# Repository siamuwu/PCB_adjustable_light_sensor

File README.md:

# Adjustable Light Sensor (LDR + 555 Timer)

## Overview

This project is an **adjustable light-sensitive switching circuit** using an LDR, a potentiometer and a 555 Timer IC. The system detects ambient light intensity and automatically turns an LED ON or OFF based on a user-defined threshold. The sensitivity of the circuit can be tuned using the potentiometer which makes it adaptable for different lighting conditions.

## Features

* Automatic light detection using LDR
* Adjustable sensitivity via potentiometer
* Stable switching using 555 Timer IC
* Simple, low-cost analog design
* Suitable for real-world automation applications

## Components Used
* LDR (Light Dependent Resistor)
* Potentiometer
* 555 Timer IC
* LED
* Resistors
* Capacitor
* Power Supply (5V–9V)

## Working Principle

The LDR and potentiometer form a voltage divider that generates a voltage corresponding to ambient light intensity. This voltage is fed into the 555 Timer IC, which operates as a comparator.

* In **bright conditions**, the LDR resistance decreases, causing the output to remain OFF.
* In **low-light conditions**, the LDR resistance increases, and once the voltage crosses the threshold set by the potentiometer, the 555 Timer switches the LED ON.

The potentiometer allows fine-tuning of the switching point, enabling precise control over when the LED activates.

## Applications

* Automatic street lighting
* Night lamps
* Light-activated switches
* Energy-efficient lighting systems
* Basic sensor interfacing projects

## What I have learnt from this project
* Basic PCB Design by KiCad
* Usage of LDR for sensing light
* Usage of 555 Timer in various applications

## Preview

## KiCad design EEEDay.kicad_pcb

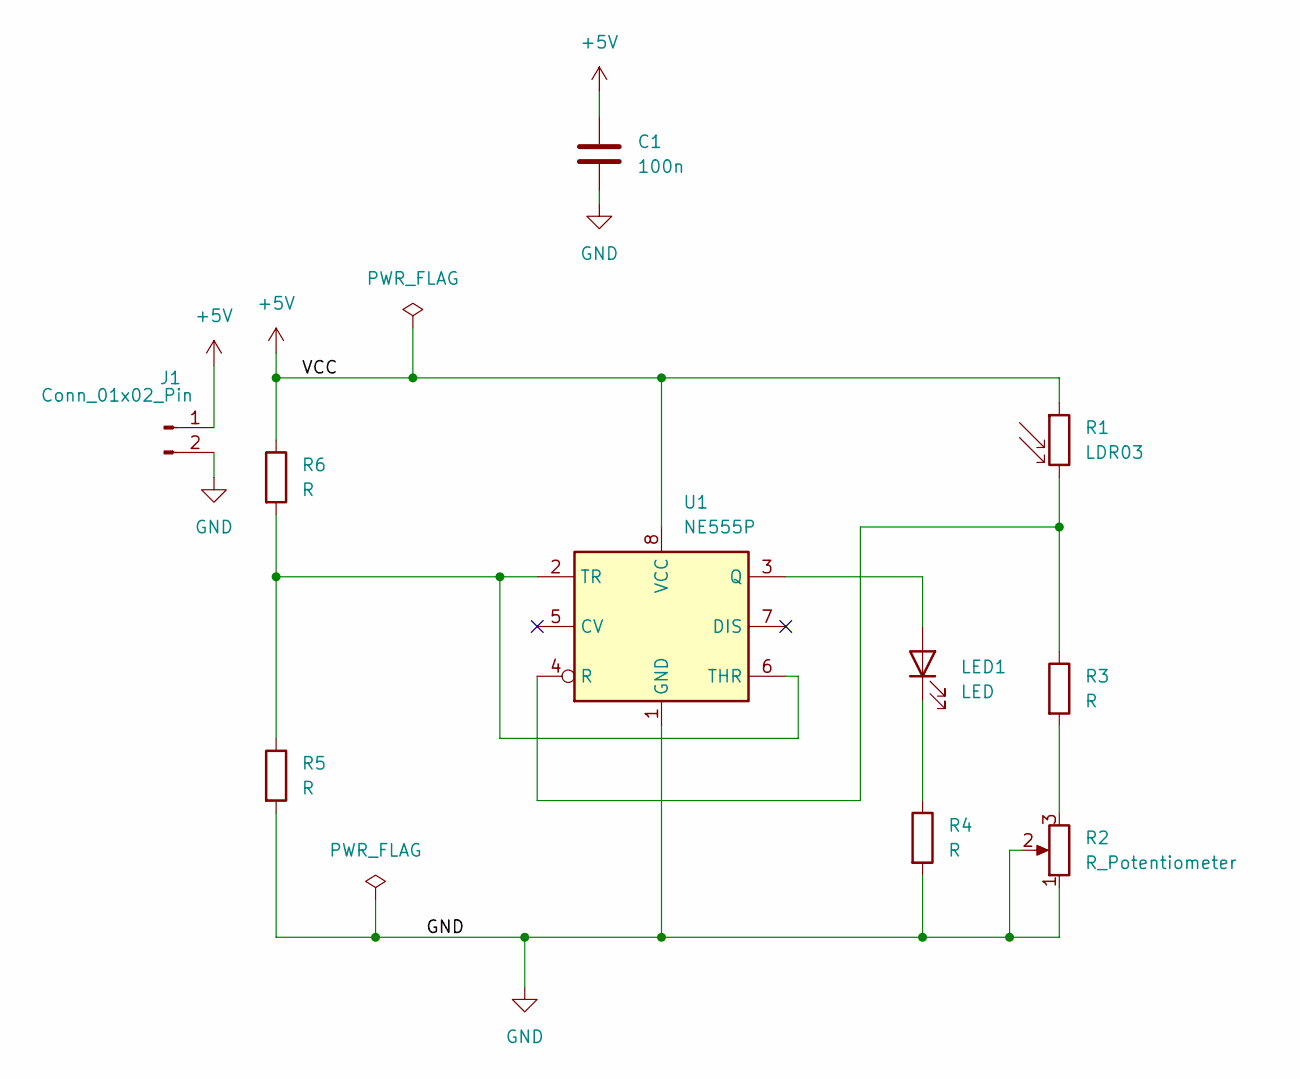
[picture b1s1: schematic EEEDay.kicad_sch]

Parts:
C1: 100n; C_Disc_D7.5mm_W5.0mm_P7.50mm
J1: Conn_01x02_Pin; AMASS_XT30PW-F_1x02_P2.50mm_Horizontal
LED1: LED; LED_D5.0mm
R1: LDR03; R_LDR_10x8.5mm_P7.6mm_Vertical
R2: R_Potentiometer; Potentiometer_Bourns_3296W_Vertical
R3, R4, R5, R6: R; R_Axial_DIN0207_L6.3mm_D2.5mm_P7.62mm_Horizontal
U1: NE555P; DIP-8_W7.62mm

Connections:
+5V: C1.1, J1.1, R1.1, R6.1, U1.8 (VCC)
GND: C1.2, J1.2, R2.1, R2.2, R4.2, R5.2, U1.1 (GND)
unnamed: LED1.2 (A), U1.3 (Q)
unnamed: LED1.1 (K), R4.1
unnamed: R2.3, R3.2
unnamed: R1.2, R3.1, U1.4 (R)
unnamed: R5.1, R6.2, U1.2 (TR), U1.6 (THR)

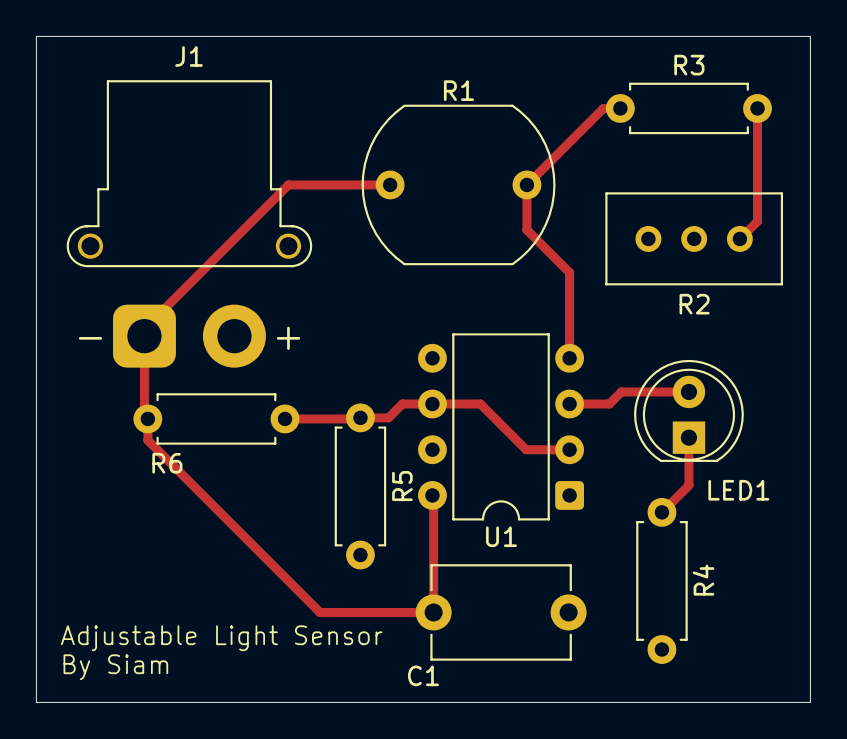
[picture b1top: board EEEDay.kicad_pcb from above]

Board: 2 copper layers, 43.0 x 37.0 mm, 10 parts (0 on the bottom side), 7 nets.

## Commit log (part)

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2026-04-15 Update README with project details and features
    Added detailed project description, features, components, working principle, and applications for the adjustable light sensor.
2026-04-15 Rename Screenshot 2026-04-15 114938.png to Images/top.png
2026-04-15 Rename Screenshot 2026-04-15 114950.png to Images/bottom.png
2026-04-15 Add images to README preview section
